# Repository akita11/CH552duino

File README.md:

# CH552duino

[WCH(南京沁恒微电子股份有限公司)](http://wch-ic.com/)の8ビットマイコン[CH552](http://wch-ic.com/products/CH552.html)を使った、Arduino UNO型のマイコンボードです。
主な特徴は以下のとおりです。

- Arduino UNO型
- [ArduinoIDEなどでプログラム開発が可能](https://qiita.com/akita11/items/d7baed4ca3c06e292637)
- USBペリフェラル（キーボードやUSBメモリなど）として動作可能
- USB Type-Cコネクタ

またArduinoUNOとは、以下のような違いがあります。
- 一部ピンの機能が異なる
- 一部未接続のソケット端子がある
- +3.3V出力の電流供給能力は100mA程度（CH552内蔵レギュレータの性能）
- リセット(RST)は正論理で、"1"でリセット
- +5V端子に、外部電源から+5Vを供給可能（内部にレギュレータはないので、+5Vを超える電圧は不可）

基板上の"LED"（オレンジ）はP1.7で駆動できます。

## ピン配置

## Author

Junichi Akita (@akita11) / akita@ifdl.jp

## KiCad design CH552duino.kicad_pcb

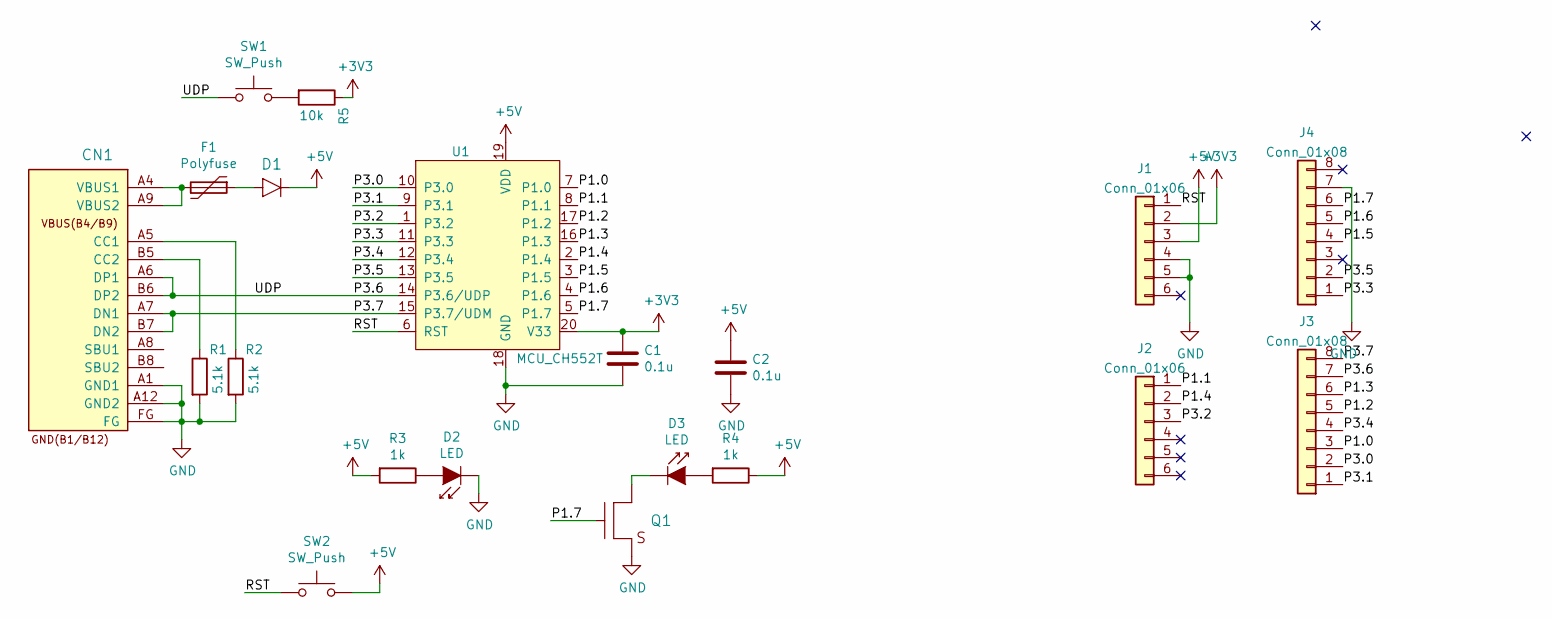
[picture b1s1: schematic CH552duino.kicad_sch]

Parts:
C1, C2: 0.1u; C_0603_1608Metric
CN1: CON_USB-C-16; USB-C_16P_TH
D1: DIODE; D_SOD123FL
D2, D3: LED; LED_0603_1608Metric
F1: Polyfuse; R_1210_3225Metric
J1, J2: Conn_01x06; PinSocket_1x06_P2.54mm_Vertical
J3, J4: Conn_01x08; PinSocket_1x08_P2.54mm_Vertical
Q1: TR_NMOS_IRLML6344; SOT-23
R1, R2: 5.1k; R_0603_1608Metric
R3, R4: 1k; R_0603_1608Metric
R5: 10k; R_0603_1608Metric
SW1, SW2: SW_Push; SW_Push_SPST_NO_Alps_SKRK
U1: MCU_CH552T; TSSOP-20_4.4x6.5mm_P0.65mm

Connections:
+3V3: C1.1, J1.2, R5.1, U1.20 (V33)
+5V: C2.1, D1.K, J1.3, R3.2, R4.1, SW2.2, U1.19 (VDD)
/P1.0: J3.3, U1.7 (P1.0)
/P1.1: J2.1, U1.8 (P1.1)
/P1.2: J3.5, U1.17 (P1.2)
/P1.3: J3.6, U1.16 (P1.3)
/P1.4: J2.2, U1.2 (P1.4)
/P1.5: J4.4, U1.3 (P1.5)
/P1.6: J4.5, U1.4 (P1.6)
/P1.7: J4.6, Q1.1 (G), U1.5 (P1.7)
/P3.0: J3.2, U1.10 (P3.0)
/P3.1: J3.1, U1.9 (P3.1)
/P3.2: J2.3, U1.1 (P3.2)
/P3.3: J4.1, U1.11 (P3.3)
/P3.4: J3.4, U1.12 (P3.4)
/P3.5: J4.2, U1.13 (P3.5)
/P3.6: CN1.A6 (DP1), CN1.B6 (DP2), J3.7, SW1.1, U1.14 (P3.6/UDP)
/P3.7: CN1.A7 (DN1), CN1.B7 (DN2), J3.8, U1.15 (P3.7/UDM)
/RST: J1.1, SW2.1, U1.6 (RST)
GND: C1.2, C2.2, CN1.A1 (GND1), CN1.A12 (GND2), CN1.FG, D2.1 (K), J1.4, J1.5, J4.7, Q1.2 (S), R1.2, R2.2, U1.18 (GND)
unnamed: CN1.A4 (VBUS1), CN1.A9 (VBUS2), F1.2
unnamed: CN1.A5 (CC1), R2.1
unnamed: CN1.B5 (CC2), R1.1
unnamed: D1.A, F1.1
unnamed: D2.2 (A), R3.1
unnamed: D3.1 (K), Q1.3 (D)
unnamed: D3.2 (A), R4.2
unnamed: R5.2, SW1.2

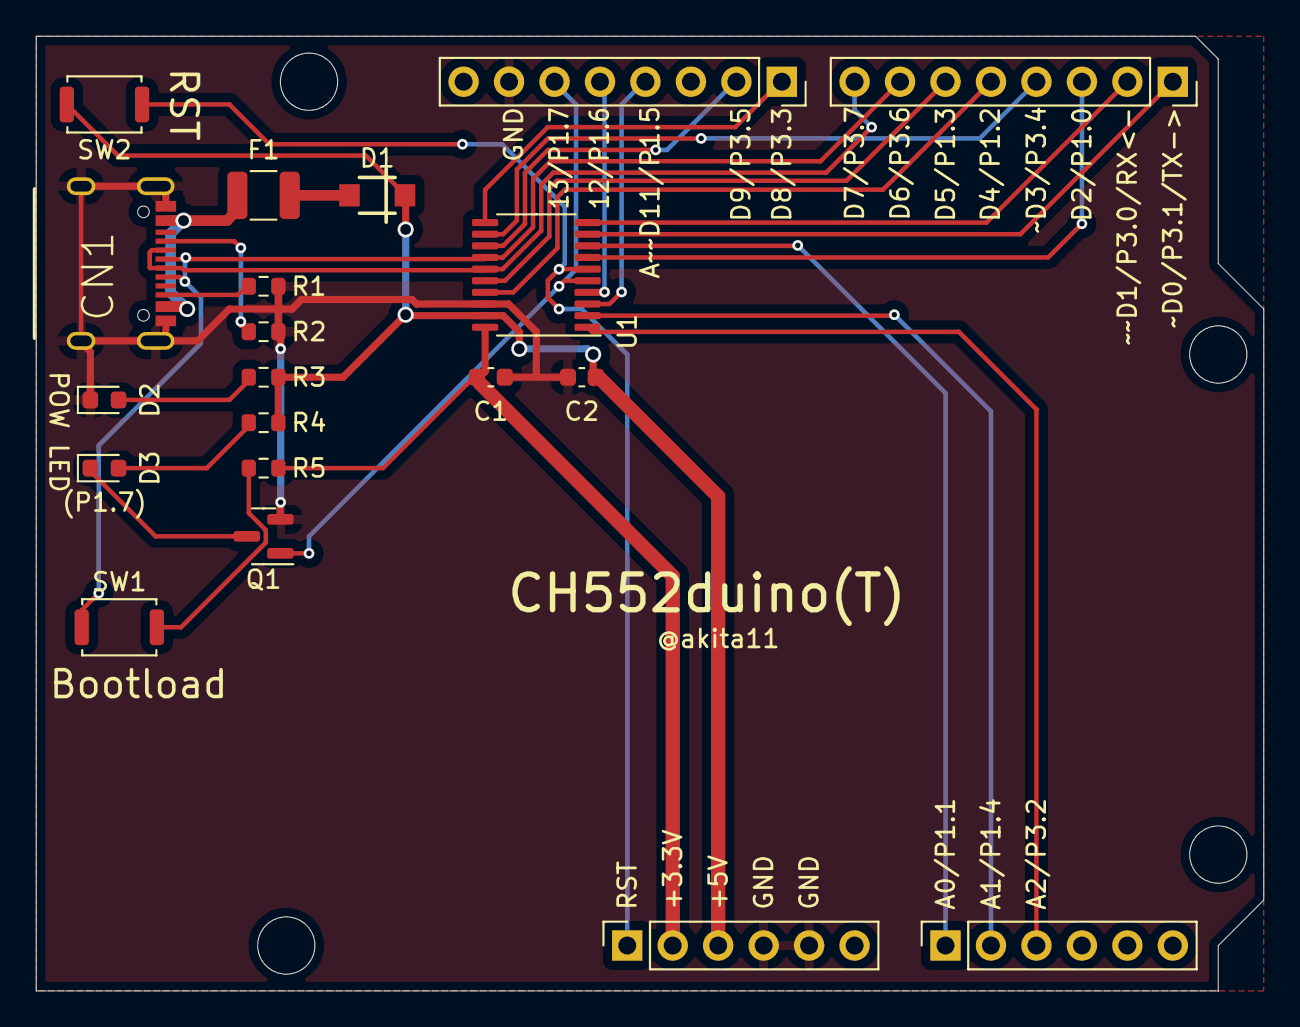
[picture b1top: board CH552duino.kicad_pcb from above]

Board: 2 copper layers, 68.6 x 53.3 mm, 20 parts (0 on the bottom side), 28 nets.

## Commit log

2022-01-19 add pin map
2022-01-19 pin map
2022-01-20 update pin map
2022-01-20 resize pin map image
2022-01-20 外部電源について追記
2022-01-26 add image
2022-01-26 add LED pin
2022-01-28 +3.3V出力電流について追記
2022-01-28 add schematic
